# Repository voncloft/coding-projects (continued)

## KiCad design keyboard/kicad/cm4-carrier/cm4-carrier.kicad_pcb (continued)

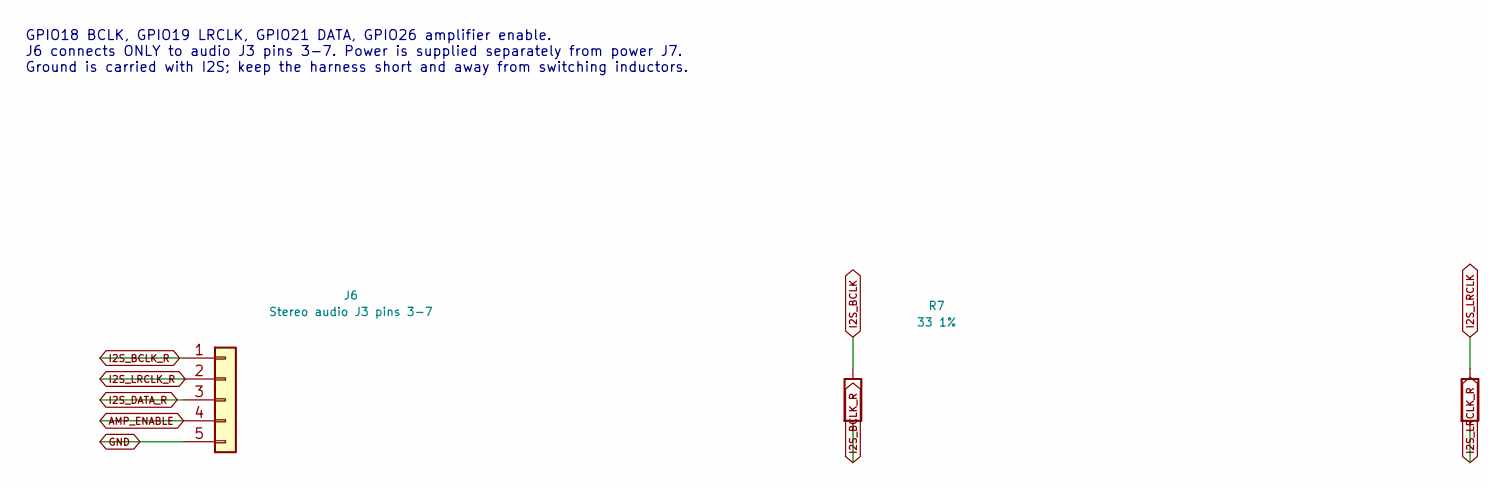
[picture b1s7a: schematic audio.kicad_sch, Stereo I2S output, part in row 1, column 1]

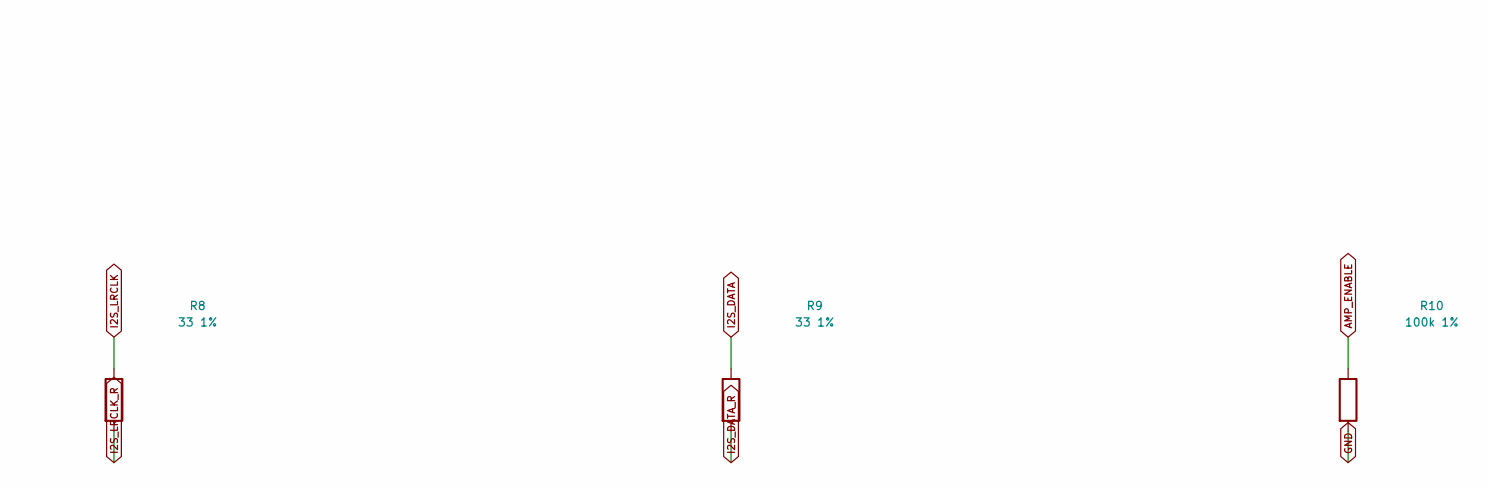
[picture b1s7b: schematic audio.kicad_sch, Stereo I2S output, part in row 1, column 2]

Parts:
J6: Stereo audio J3 pins 3-7; JST_GH_BM05B-GHS-TBT_1x05-1MP_P1.25mm_Vertical
R7, R8, R9: 33 1%; R_0603_1608Metric
R10: 100k 1%; R_0603_1608Metric

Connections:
AMP_ENABLE: J6.4, R10.1; also elsewhere on the board
GND: J6.5, R10.2; also elsewhere on the board
I2S_BCLK: R7.1; also elsewhere on the board
I2S_BCLK_R: J6.1, R7.2
I2S_DATA: R9.1; also elsewhere on the board
I2S_DATA_R: J6.3, R9.2
I2S_LRCLK: R8.1; also elsewhere on the board
I2S_LRCLK_R: J6.2, R8.2

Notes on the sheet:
GPIO18 BCLK, GPIO19 LRCLK, GPIO21 DATA, GPIO26 amplifier enable. J6 connects ONLY to audio J3 pins 3-7. Power is supplied separately from power J7. Ground is carried with I2S; keep the harness short and away from switching inductors.

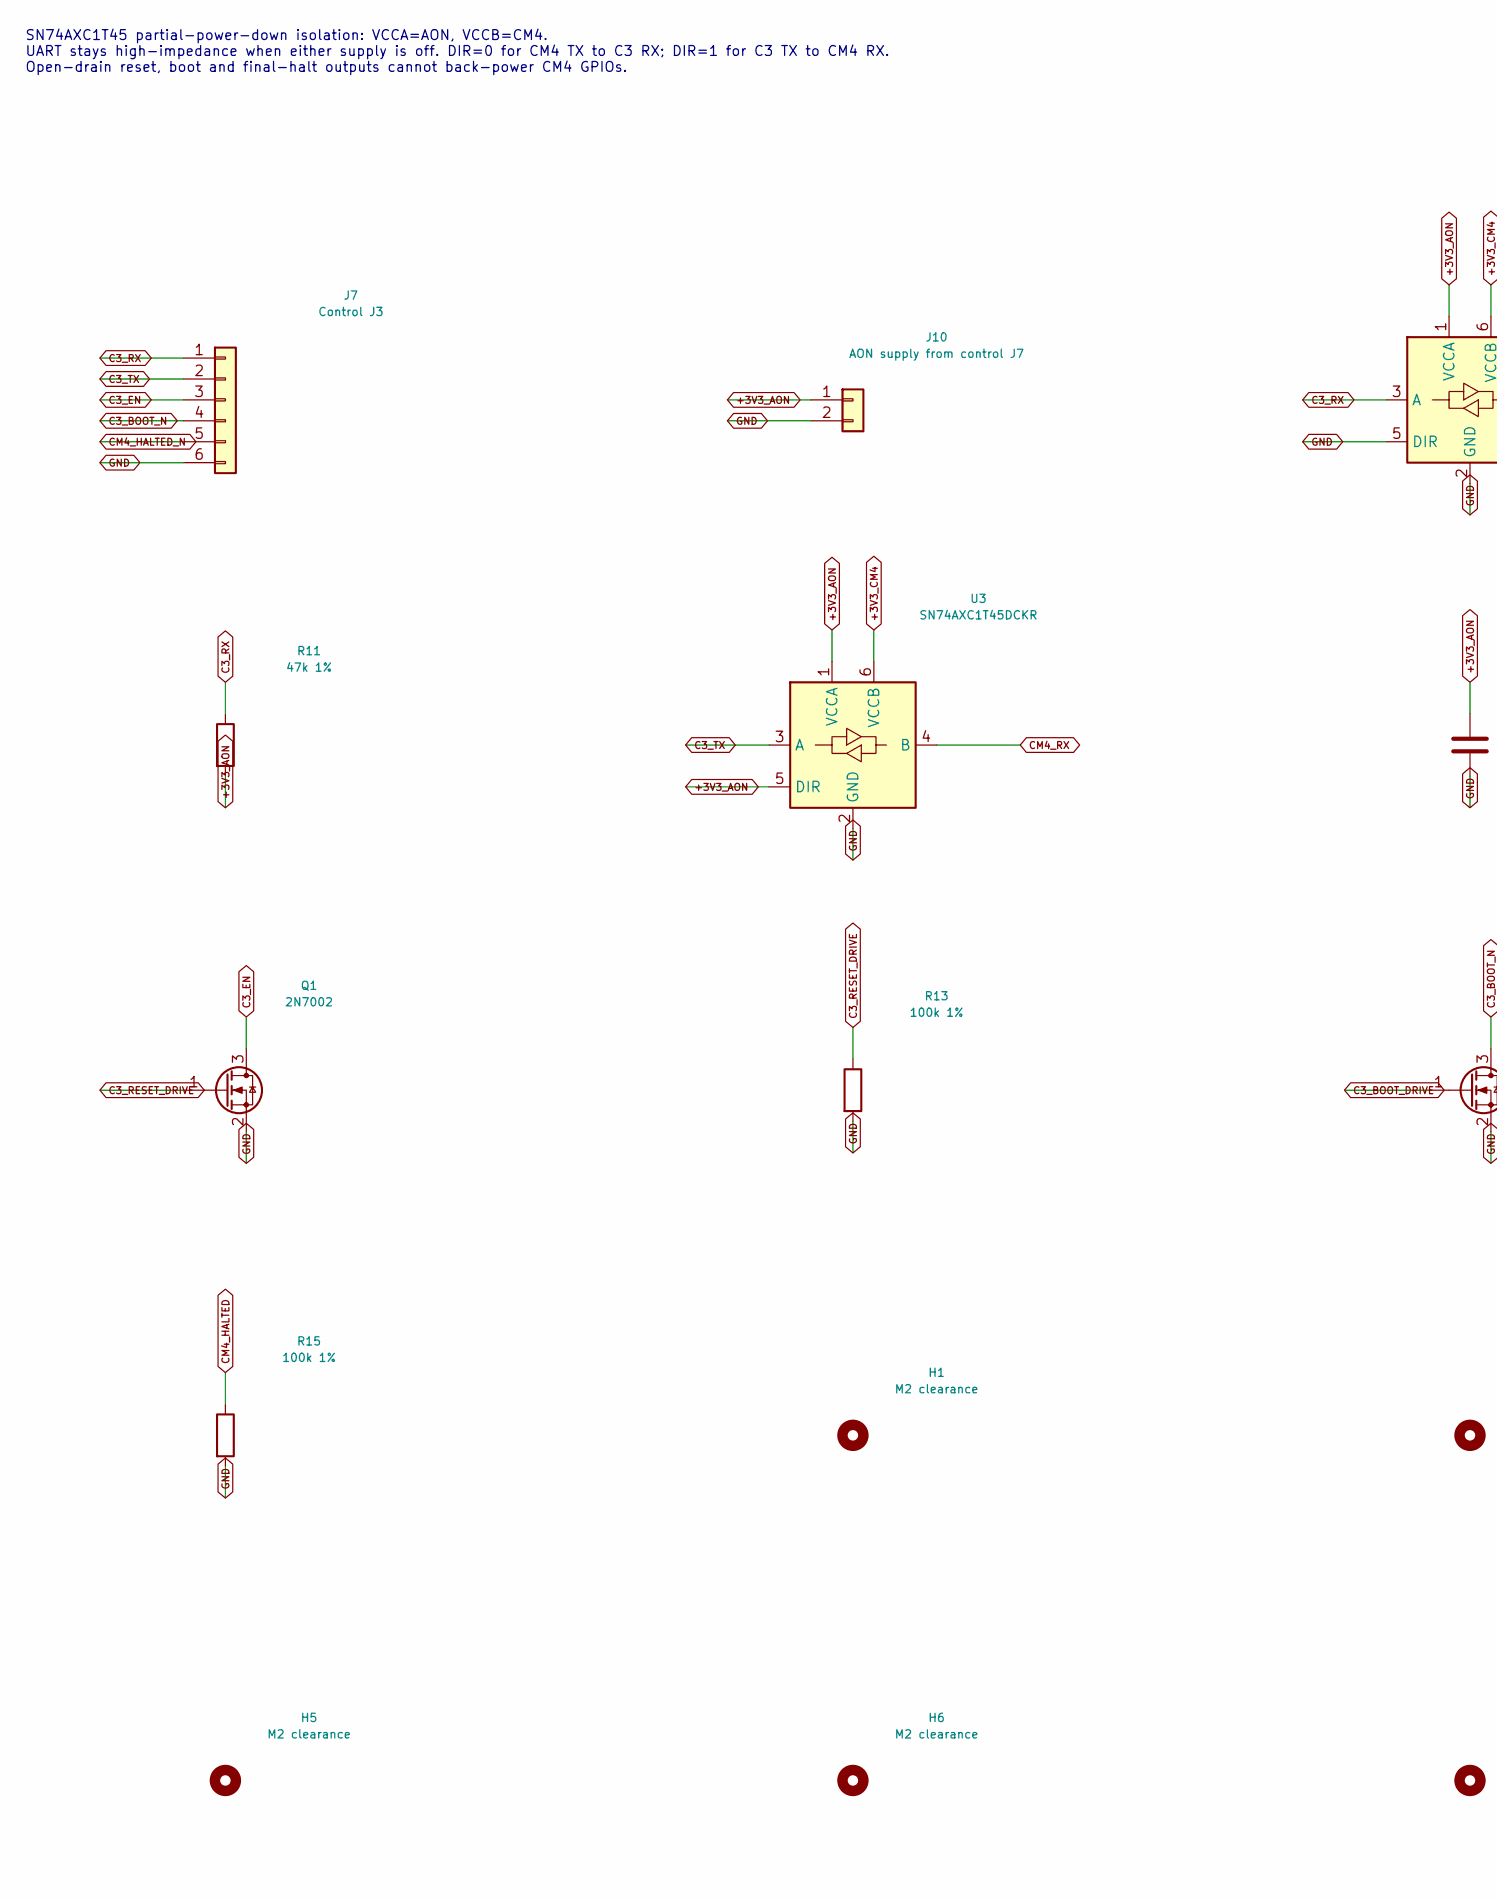
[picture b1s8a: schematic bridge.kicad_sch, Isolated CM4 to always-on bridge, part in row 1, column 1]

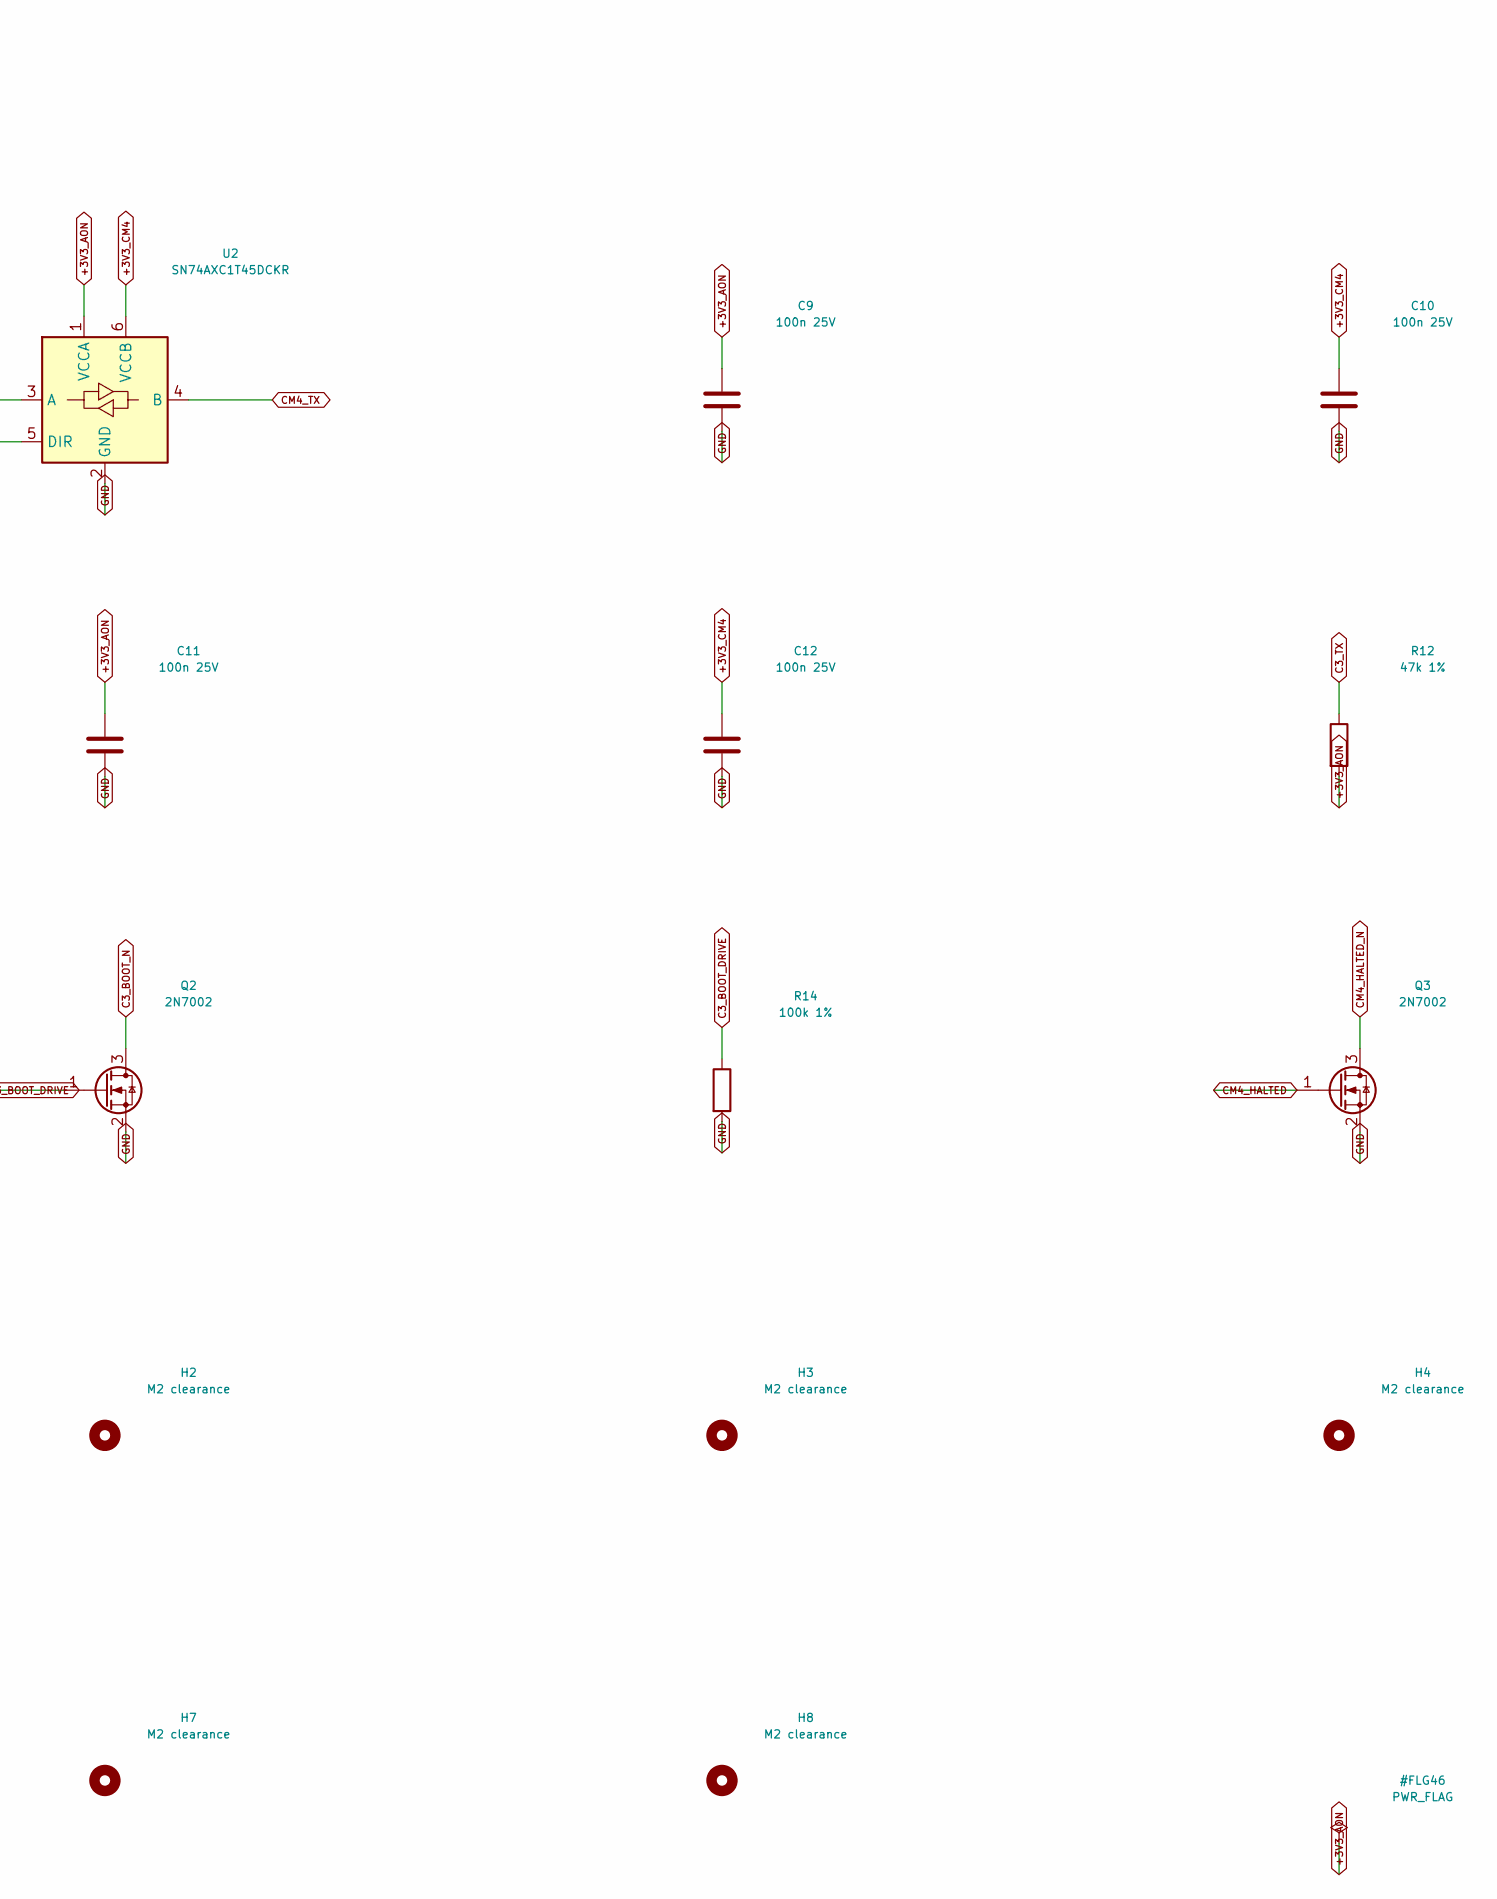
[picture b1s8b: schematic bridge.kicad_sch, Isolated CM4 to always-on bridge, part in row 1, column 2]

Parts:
C9, C10, C11, C12: 100n 25V; C_0603_1608Metric
H1, H2, H3, H4, H5, H6, H7, H8: M2 clearance; MountingHole_2.2mm_M2
J7: Control J3; JST_GH_BM06B-GHS-TBT_1x06-1MP_P1.25mm_Vertical
J10: AON supply from control J7; JST_GH_BM02B-GHS-TBT_1x02-1MP_P1.25mm_Vertical
Q1, Q2, Q3: 2N7002; SOT-23; MPN 2N7002
R11, R12: 47k 1%; R_0603_1608Metric
R13, R14, R15: 100k 1%; R_0603_1608Metric
U2, U3: SN74AXC1T45DCKR; SOT-363_SC-70-6; MPN SN74AXC1T45DCKR

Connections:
+3V3_AON: C9.1, C11.1, J10.1, R11.2, R12.2, U2.1 (VCCA), U3.1 (VCCA), U3.5 (DIR)
+3V3_CM4: C10.1, C12.1, U2.6 (VCCB), U3.6 (VCCB); also elsewhere on the board
C3_BOOT_DRIVE: Q2.1 (G), R14.1; also elsewhere on the board
C3_BOOT_N: J7.4, Q2.3 (D)
C3_EN: J7.3, Q1.3 (D)
C3_RESET_DRIVE: Q1.1 (G), R13.1; also elsewhere on the board
C3_RX: J7.1, R11.1, U2.3 (A)
C3_TX: J7.2, R12.1, U3.3 (A)
CM4_HALTED: Q3.1 (G), R15.1; also elsewhere on the board
CM4_HALTED_N: J7.5, Q3.3 (D)
CM4_RX: U3.4 (B); also elsewhere on the board
CM4_TX: U2.4 (B); also elsewhere on the board
GND: C9.2, C10.2, C11.2, C12.2, J7.6, J10.2, Q1.2 (S), Q2.2 (S), Q3.2 (S), R13.2, R14.2, R15.2, U2.2 (GND), U2.5 (DIR), U3.2 (GND); also elsewhere on the board

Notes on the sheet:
SN74AXC1T45 partial-power-down isolation: VCCA=AON, VCCB=CM4. UART stays high-impedance when either supply is off. DIR=0 for CM4 TX to C3 RX; DIR=1 for C3 TX to CM4 RX. Open-drain reset, boot and final-halt outputs cannot back-power CM4 GPIOs.

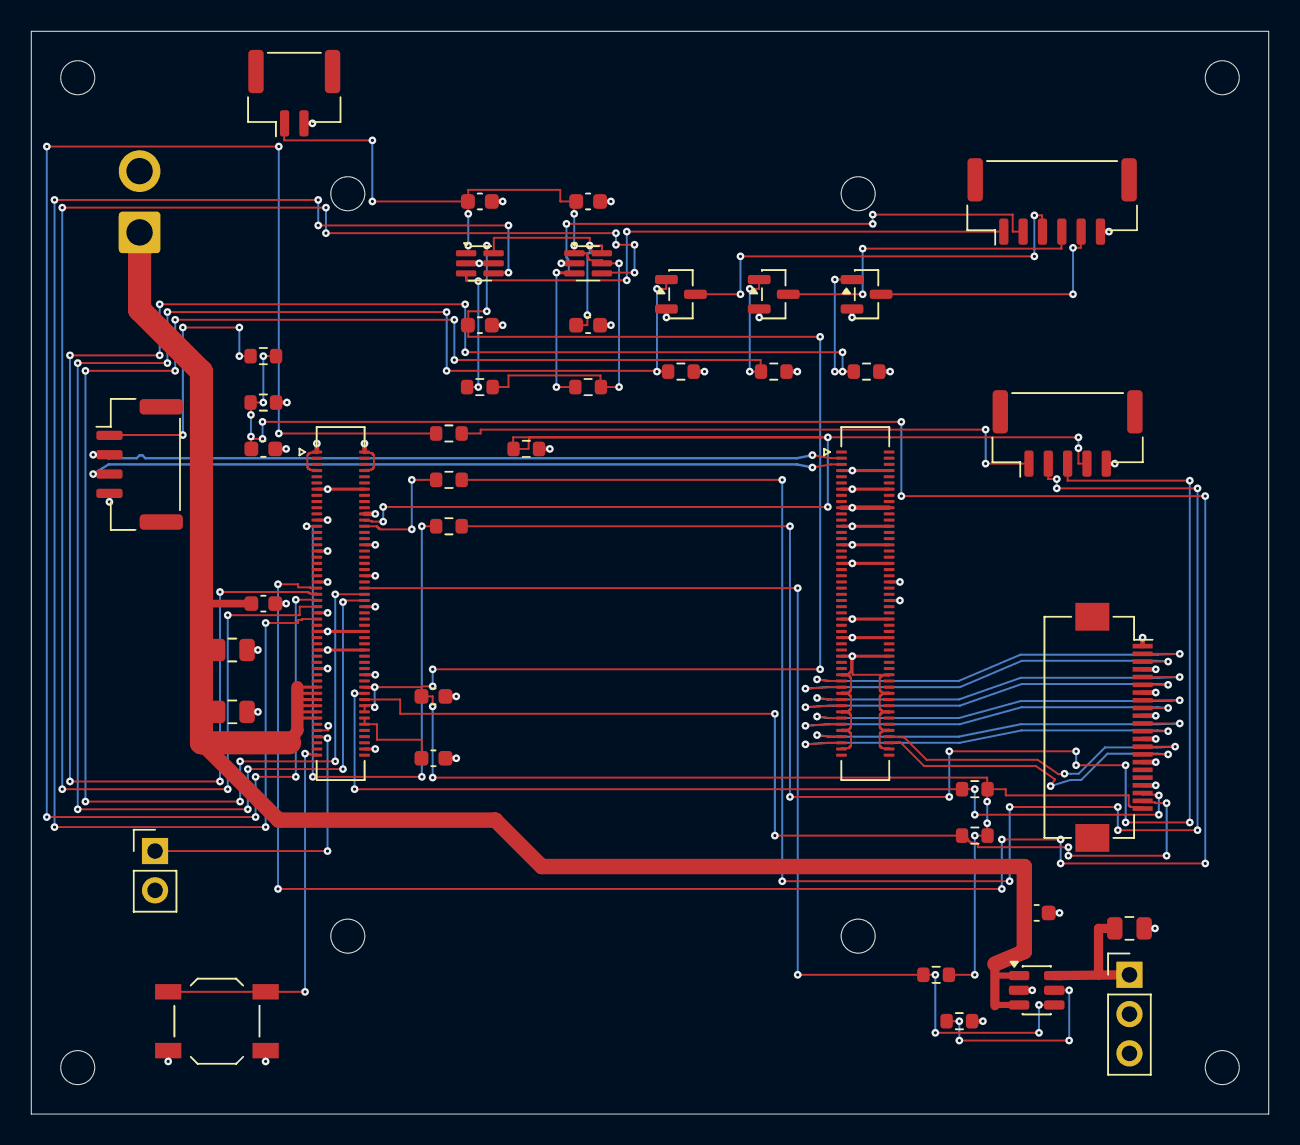
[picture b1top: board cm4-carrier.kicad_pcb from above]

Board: 4 copper layers, 80.0 x 70.0 mm, 52 parts (0 on the bottom side), 43 nets.

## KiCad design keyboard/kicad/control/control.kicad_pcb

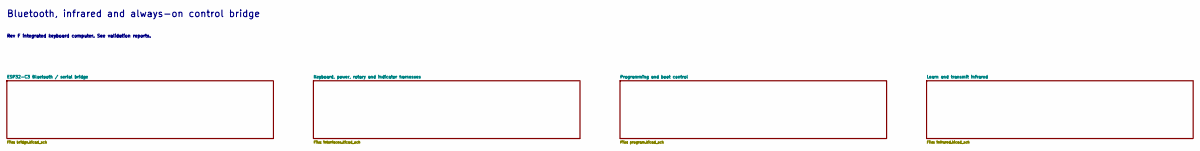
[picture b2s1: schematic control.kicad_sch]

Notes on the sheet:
Bluetooth, infrared and always-on control bridge
Rev F integrated keyboard computer. See validation reports.

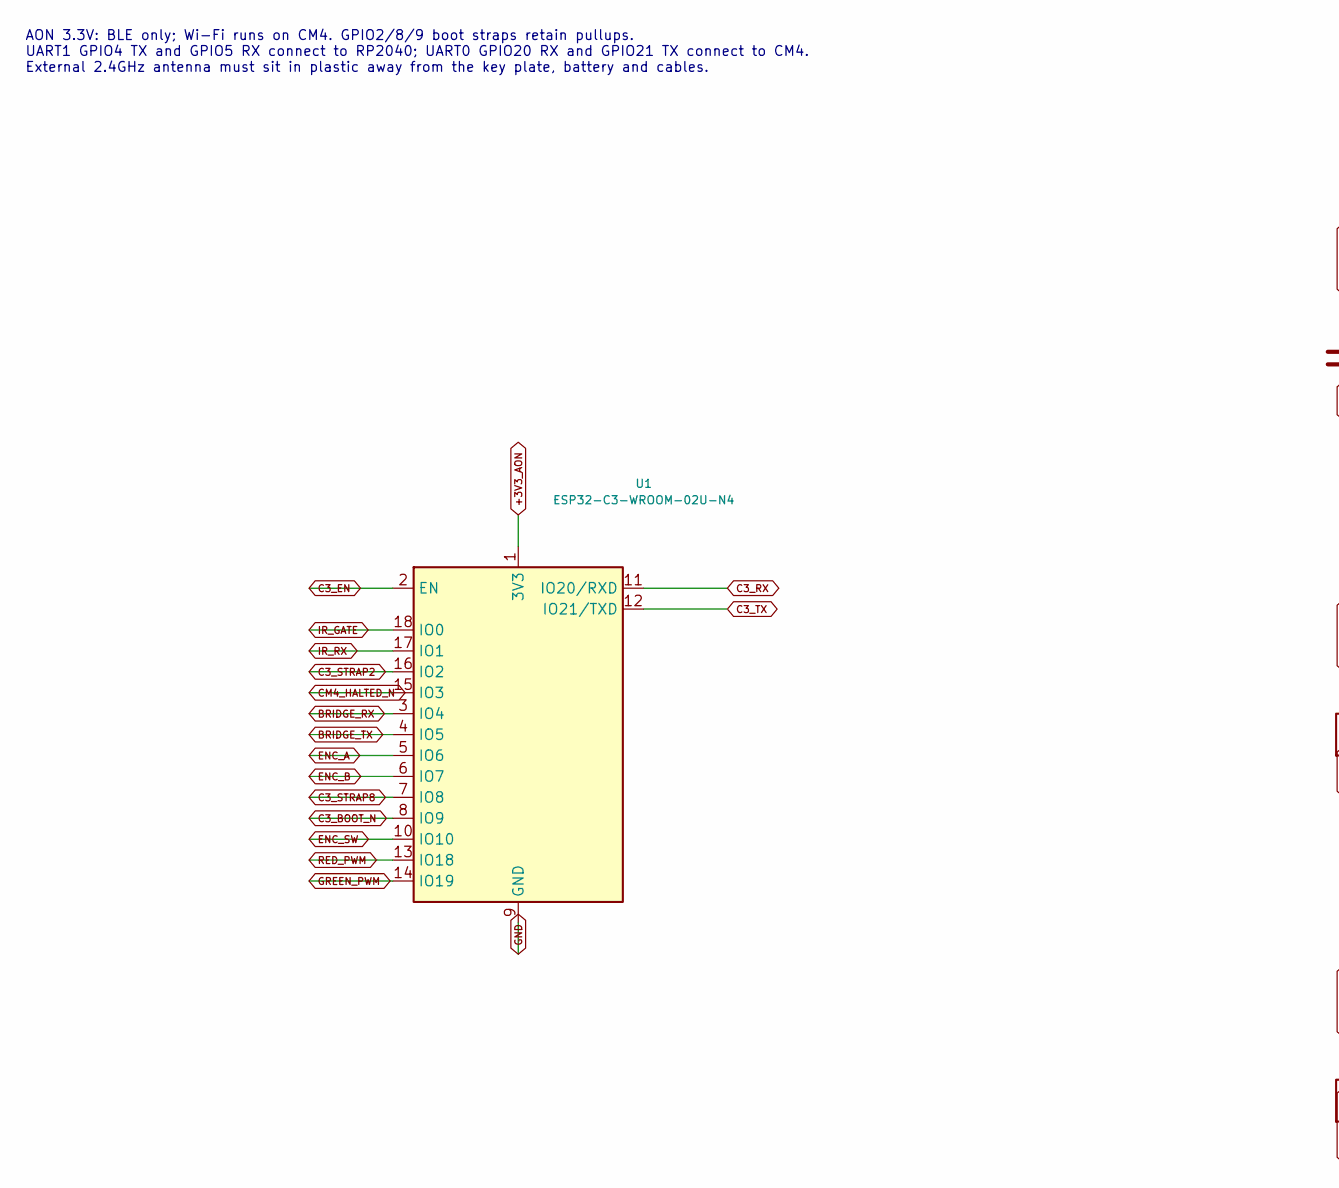
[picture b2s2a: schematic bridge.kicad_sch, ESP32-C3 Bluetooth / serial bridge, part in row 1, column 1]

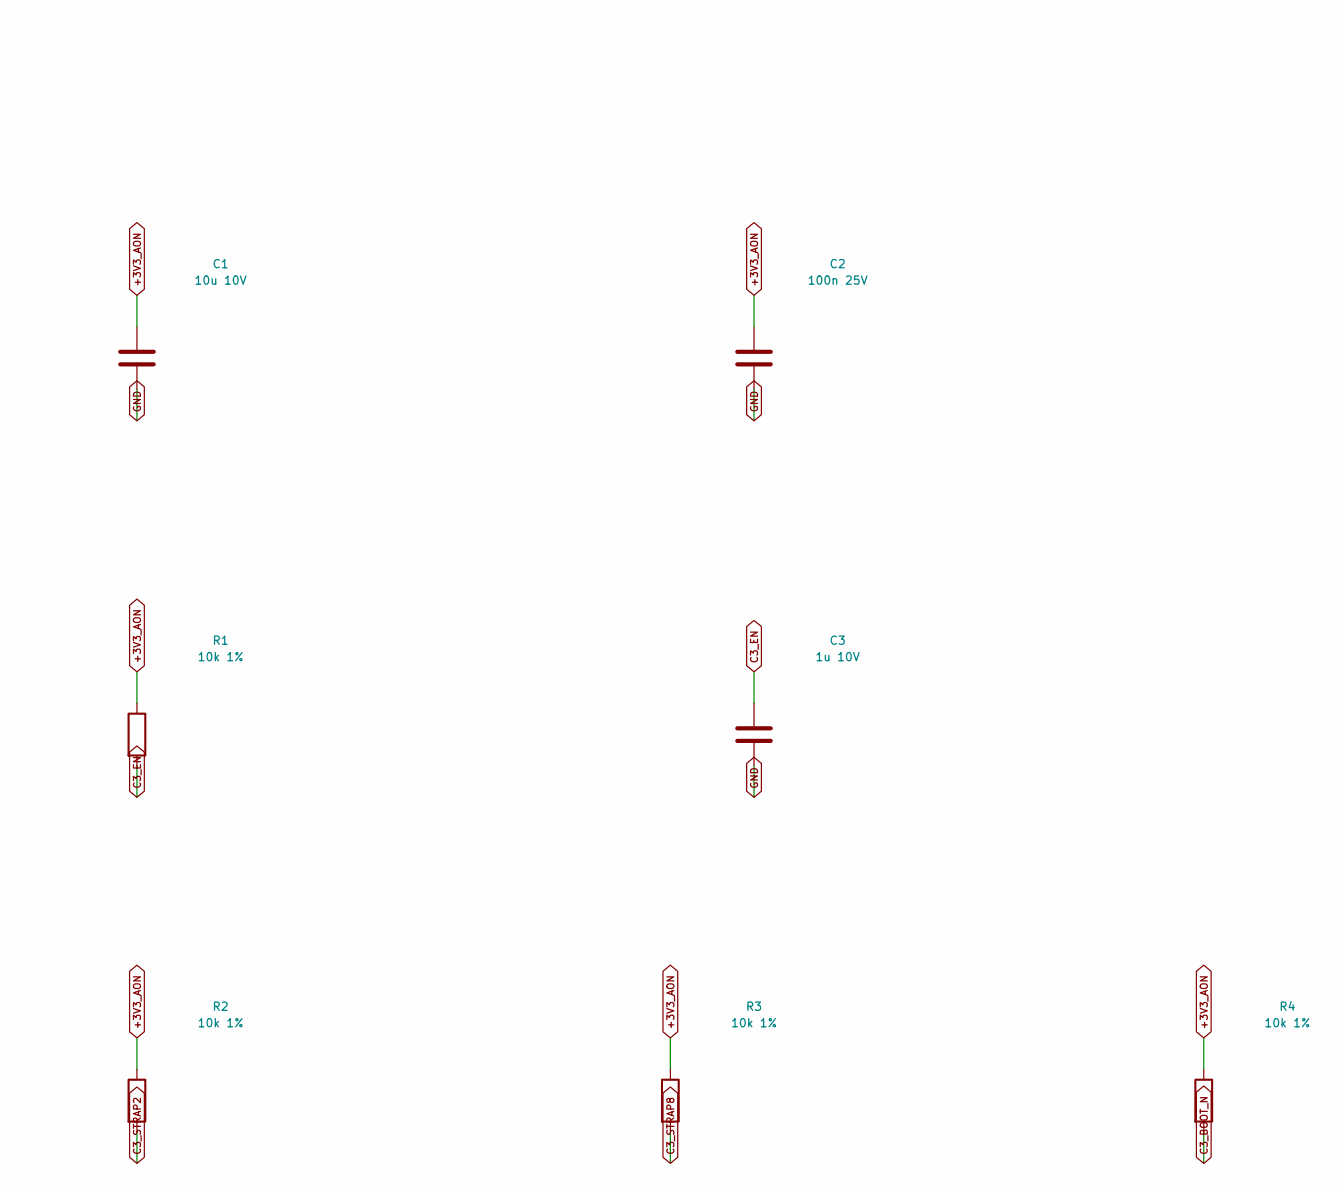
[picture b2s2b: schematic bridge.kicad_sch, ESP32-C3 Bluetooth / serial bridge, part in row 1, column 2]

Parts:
C1: 10u 10V; C_0805_2012Metric
C2: 100n 25V; C_0603_1608Metric
C3: 1u 10V; C_0603_1608Metric
R1, R2, R3, R4: 10k 1%; R_0603_1608Metric
U1: ESP32-C3-WROOM-02U-N4; ESP32-C3-WROOM-02U; MPN ESP32-C3-WROOM-02U-N4

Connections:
+3V3_AON: C1.1, C2.1, R1.1, R2.1, R3.1, R4.1, U1.1 (3V3); also elsewhere on the board
BRIDGE_RX: U1.3 (IO4); also elsewhere on the board
BRIDGE_TX: U1.4 (IO5); also elsewhere on the board
C3_BOOT_N: R4.2, U1.8 (IO9); also elsewhere on the board
C3_EN: C3.1, R1.2, U1.2 (EN); also elsewhere on the board
C3_RX: U1.11 (IO20/RXD); also elsewhere on the board
C3_STRAP2: R2.2, U1.16 (IO2)
C3_STRAP8: R3.2, U1.7 (IO8)
C3_TX: U1.12 (IO21/TXD); also elsewhere on the board
CM4_HALTED_N: U1.15 (IO3); also elsewhere on the board
ENC_A: U1.5 (IO6); also elsewhere on the board
ENC_B: U1.6 (IO7); also elsewhere on the board
ENC_SW: U1.10 (IO10); also elsewhere on the board
GND: C1.2, C2.2, C3.2, U1.9 (GND), U1.19 (GND); also elsewhere on the board
GREEN_PWM: U1.14 (IO19); also elsewhere on the board
IR_GATE: U1.18 (IO0); also elsewhere on the board
IR_RX: U1.17 (IO1); also elsewhere on the board
RED_PWM: U1.13 (IO18); also elsewhere on the board

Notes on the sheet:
AON 3.3V: BLE only; Wi-Fi runs on CM4. GPIO2/8/9 boot straps retain pullups. UART1 GPIO4 TX and GPIO5 RX connect to RP2040; UART0 GPIO20 RX and GPIO21 TX connect to CM4. External 2.4GHz antenna must sit in plastic away from the key plate, battery and cables.

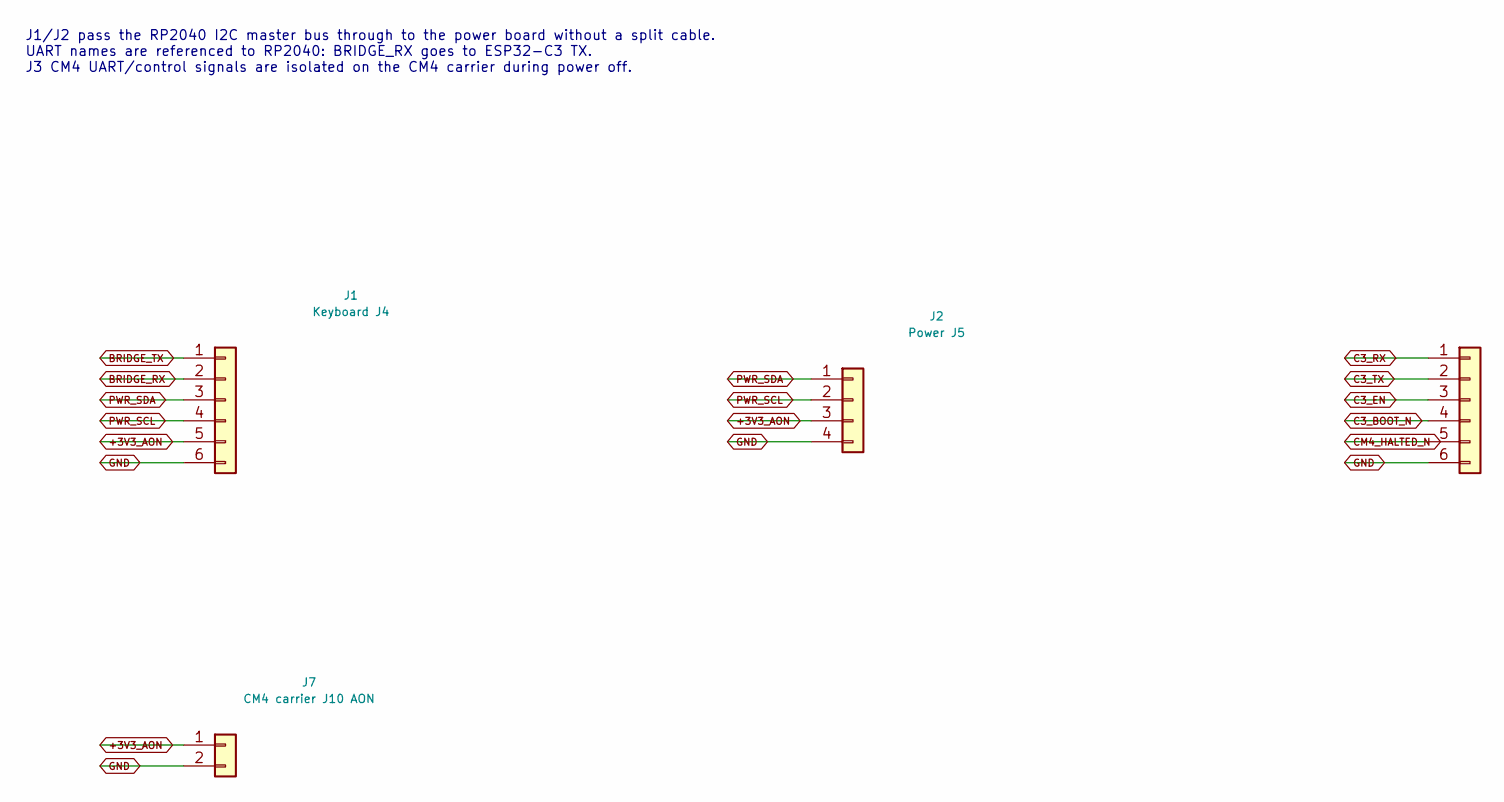
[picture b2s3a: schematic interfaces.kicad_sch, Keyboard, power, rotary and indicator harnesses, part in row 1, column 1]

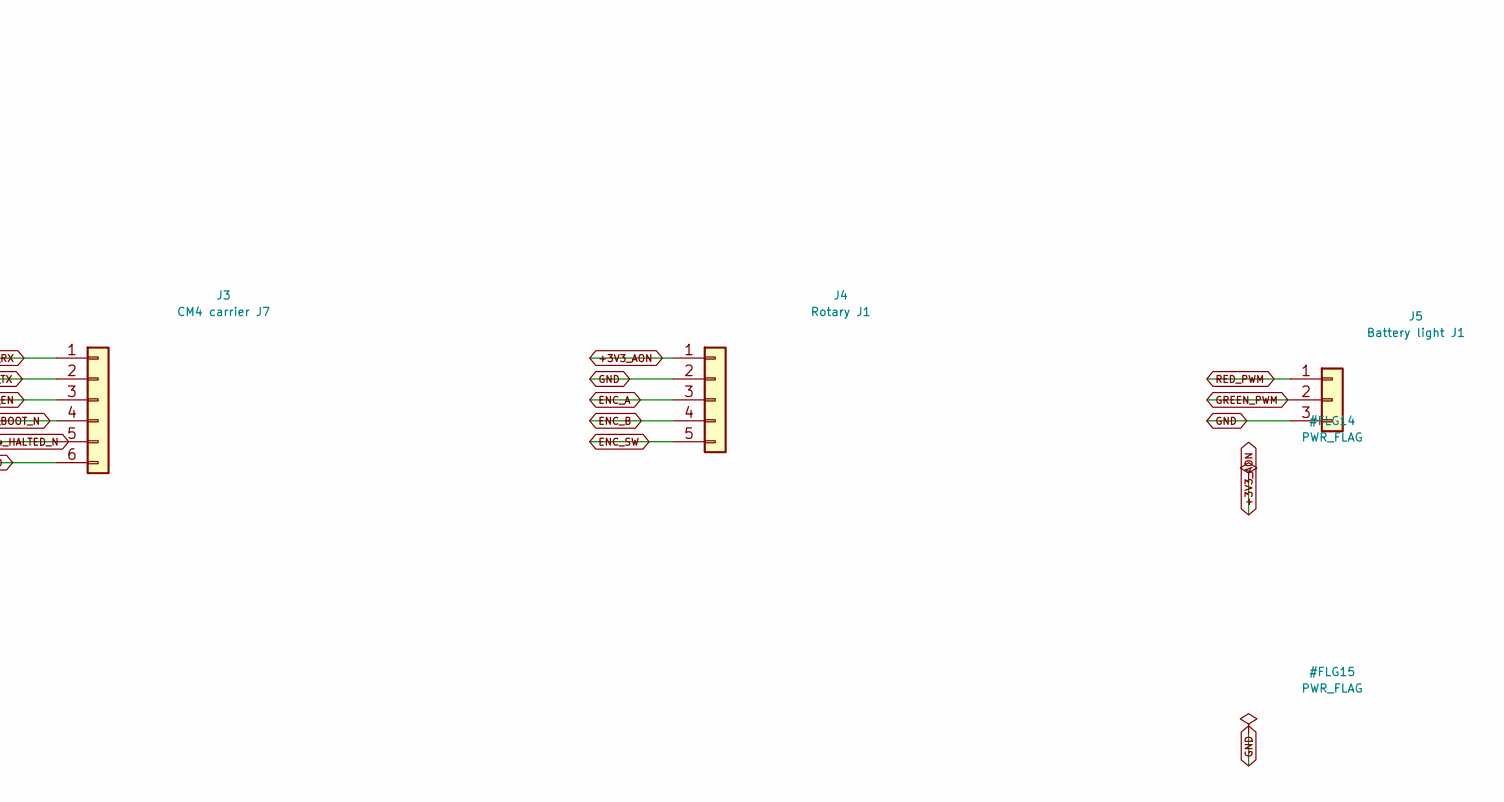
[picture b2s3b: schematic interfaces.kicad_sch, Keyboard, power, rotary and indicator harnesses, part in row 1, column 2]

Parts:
J1: Keyboard J4; JST_GH_BM06B-GHS-TBT_1x06-1MP_P1.25mm_Vertical
J2: Power J5; JST_GH_BM04B-GHS-TBT_1x04-1MP_P1.25mm_Vertical
J3: CM4 carrier J7; JST_GH_BM06B-GHS-TBT_1x06-1MP_P1.25mm_Vertical
J4: Rotary J1; JST_GH_BM05B-GHS-TBT_1x05-1MP_P1.25mm_Vertical
J5: Battery light J1; JST_GH_BM03B-GHS-TBT_1x03-1MP_P1.25mm_Vertical
J7: CM4 carrier J10 AON; JST_GH_BM02B-GHS-TBT_1x02-1MP_P1.25mm_Vertical

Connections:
+3V3_AON: J1.5, J2.3, J4.1, J7.1; also elsewhere on the board
BRIDGE_RX: J1.2; also elsewhere on the board
BRIDGE_TX: J1.1; also elsewhere on the board
C3_BOOT_N: J3.4; also elsewhere on the board
C3_EN: J3.3; also elsewhere on the board
C3_RX: J3.1; also elsewhere on the board
C3_TX: J3.2; also elsewhere on the board
CM4_HALTED_N: J3.5; also elsewhere on the board
ENC_A: J4.3; also elsewhere on the board
ENC_B: J4.4; also elsewhere on the board
ENC_SW: J4.5; also elsewhere on the board
GND: J1.6, J2.4, J3.6, J4.2, J5.3, J7.2; also elsewhere on the board
GREEN_PWM: J5.2; also elsewhere on the board
PWR_SCL: J1.4, J2.2
PWR_SDA: J1.3, J2.1
RED_PWM: J5.1; also elsewhere on the board

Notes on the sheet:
J1/J2 pass the RP2040 I2C master bus through to the power board without a split cable. UART names are referenced to RP2040: BRIDGE_RX goes to ESP32-C3 TX. J3 CM4 UART/control signals are isolated on the CM4 carrier during power off.

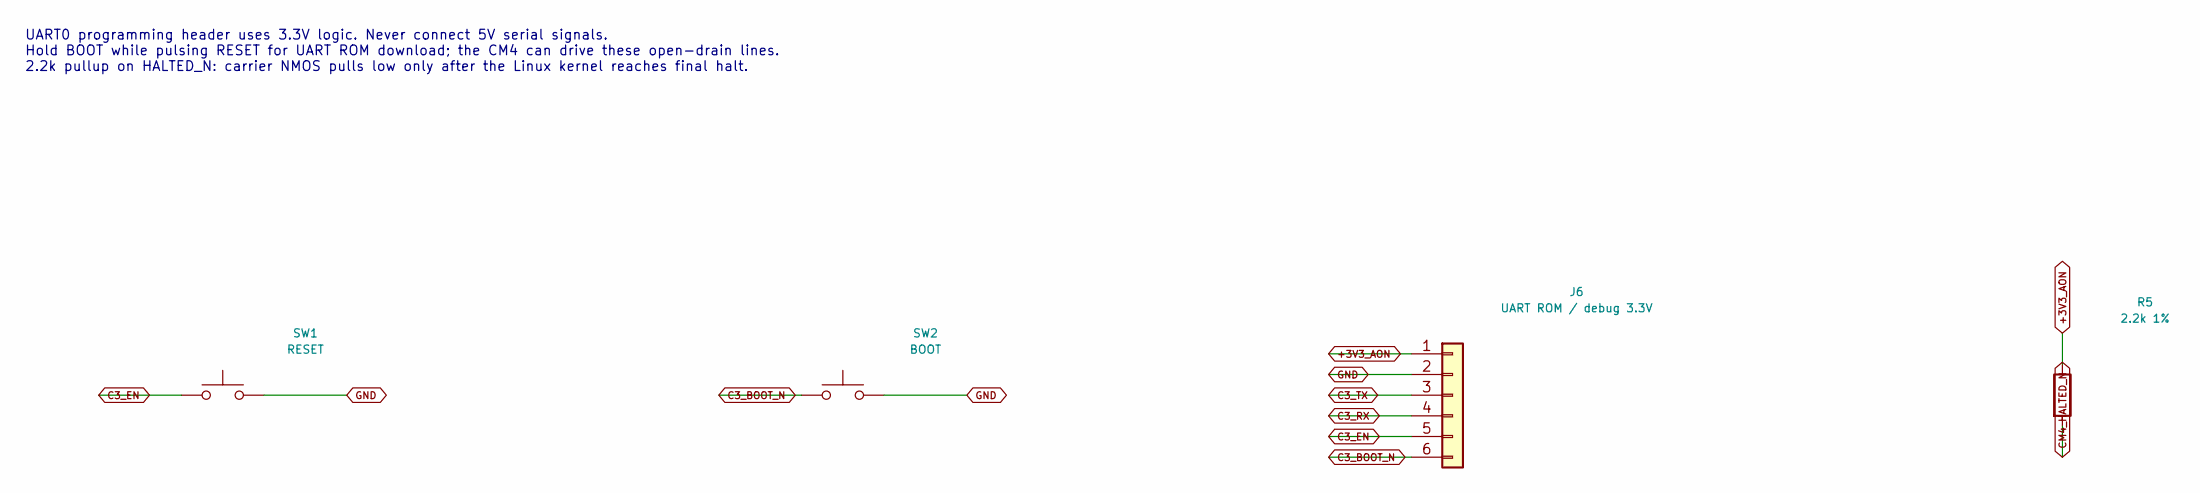
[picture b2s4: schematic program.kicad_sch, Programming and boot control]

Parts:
J6: UART ROM / debug 3.3V; JST_GH_BM06B-GHS-TBT_1x06-1MP_P1.25mm_Vertical
R5: 2.2k 1%; R_0603_1608Metric
SW1: RESET; SW_SPST_TL3342; MPN TL3342F160QG
SW2: BOOT; SW_SPST_TL3342; MPN TL3342F160QG

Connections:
+3V3_AON: J6.1, R5.1; also elsewhere on the board
C3_BOOT_N: J6.6, SW2.1; also elsewhere on the board
C3_EN: J6.5, SW1.1; also elsewhere on the board
C3_RX: J6.4; also elsewhere on the board
C3_TX: J6.3; also elsewhere on the board
CM4_HALTED_N: R5.2; also elsewhere on the board
GND: J6.2, SW1.2, SW2.2; also elsewhere on the board

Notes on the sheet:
UART0 programming header uses 3.3V logic. Never connect 5V serial signals. Hold BOOT while pulsing RESET for UART ROM download; the CM4 can drive these open-drain lines. 2.2k pullup on HALTED_N: carrier NMOS pulls low only after the Linux kernel reaches final halt.
